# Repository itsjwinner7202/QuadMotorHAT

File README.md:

# QuadMotorHAT

A simple Raspberry Pi HAT for controlling four DC motors.

## Why I made it

While making my WRO robot, I ran into a problem: I needed to control multiple motors from a Raspberry Pi without a mess of separate boards and wiring.

There are already plenty of motor HATs available, but I wanted something simple that fit what I needed. So I decided to design my own.

## Features

* **4 motor control** — Control four motors from the Raspberry Pi using the included Python library.
* **Screw terminals** — Secure connections for the motors and power.
* **Compact design** — Keeps a low profile while leaving enough room for a cooling fan on the Raspberry Pi.
* **Simple Python control** — Control the motors directly from your Python project.

## Python Library

The repository includes `quadmotorhat.py`, which provides a simple interface for controlling the four motors.

First, install `gpiozero`:

```bash
pip install gpiozero
```

Then place `quadmotorhat.py` in the same directory as your Python program:

```text
your_project/
├── quadmotorhat.py
└── main.py
```

Import the motor controls:

```python
from quadmotorhat import M1, M2, M3, M4
```

You can then use `M1`, `M2`, `M3`, and `M4` to control the four motor outputs.

## PCB Files

The full board design is included in the repository.

* `QuadMotorHAT.kicad_sch` — Schematic
* `QuadMotorHAT.kicad_pcb` — PCB layout
* `QuadMotorHAT.kicad_pro` — KiCad project

You can open these files in KiCad to inspect or modify the design.

## License

This project is licensed under the terms of the license included in this repository.

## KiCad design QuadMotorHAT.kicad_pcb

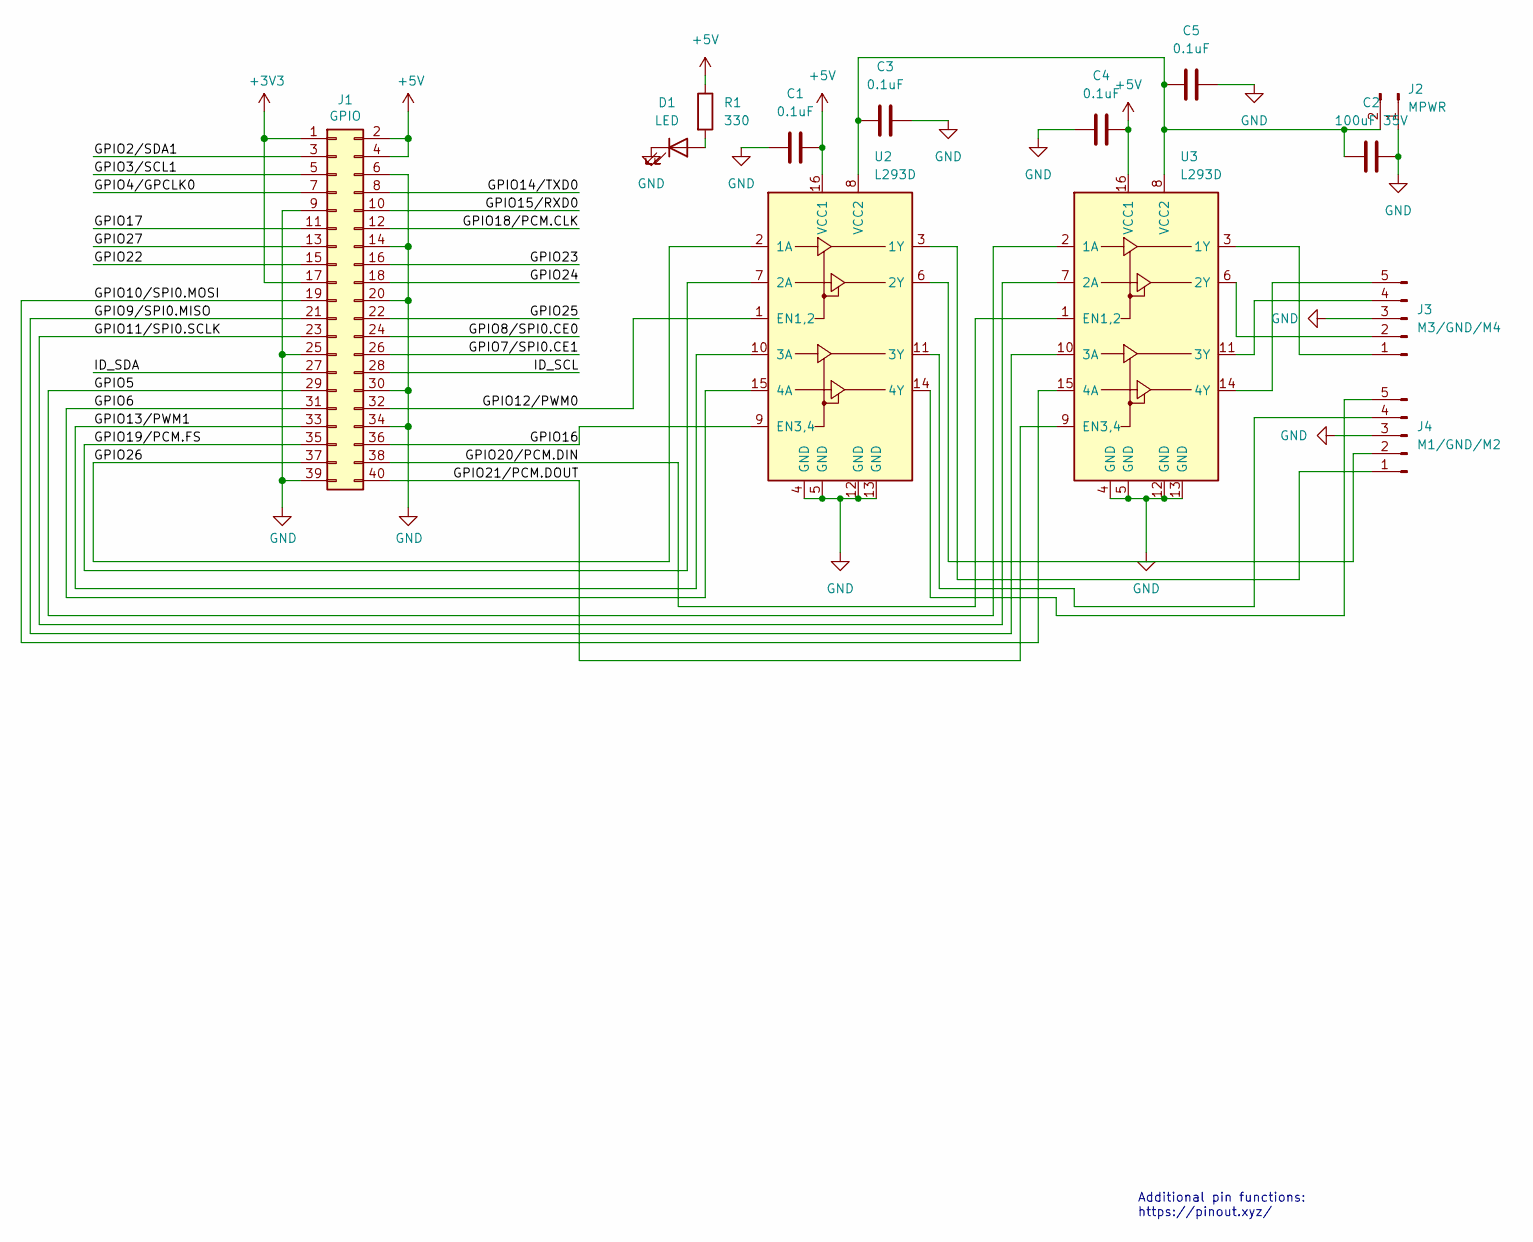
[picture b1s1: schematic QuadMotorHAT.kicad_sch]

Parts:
C1, C3, C4, C5: 0.1uF; C_0805_2012Metric
C2: 100uF 35V; CP_Radial_D6.3mm_P2.50mm
D1: LED; LED_0805_2012Metric
J1: GPIO; PinSocket_2x20_P2.54mm_Vertical
J2: MPWR; TerminalBlock_Phoenix_MKDS-1,5-2_1x02_P5.00mm_Horizontal
J3: M3/GND/M4; TerminalBlock_Phoenix_MKDS-1,5-5_1x05_P5.00mm_Horizontal
J4: M1/GND/M2; TerminalBlock_Phoenix_MKDS-1,5-5_1x05_P5.00mm_Horizontal
R1: 330; R_0805_2012Metric
U2, U3: L293D; DIP-16_W7.62mm

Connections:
+3V3: J1.1, J1.17
+5V: C1.2, C4.2, J1.2, J1.4, R1.1, U2.16 (VCC1), U3.16 (VCC1)
/GPIO2/SDA1: J1.3
/GPIO3/SCL1: J1.5
/GPIO4/GPCLK0: J1.7
/GPIO5: J1.29, U3.2 (1A)
/GPIO6: J1.31, U2.15 (4A)
/GPIO7/SPI0.CE1: J1.26
/GPIO8/SPI0.CE0: J1.24
/GPIO9/SPI0.MISO: J1.21, U3.10 (3A)
/GPIO10/SPI0.MOSI: J1.19, U3.15 (4A)
/GPIO11/SPI0.SCLK: J1.23, U3.7 (2A)
/GPIO12/PWM0: J1.32, U2.1 (EN1,2)
/GPIO13/PWM1: J1.33, U2.10 (3A)
/GPIO14/TXD0: J1.8
/GPIO15/RXD0: J1.10
/GPIO16: J1.36, U2.9 (EN3,4)
/GPIO17: J1.11
/GPIO18/PCM.CLK: J1.12
/GPIO19/PCM.FS: J1.35, U2.7 (2A)
/GPIO20/PCM.DIN: J1.38, U3.1 (EN1,2)
/GPIO21/PCM.DOUT: J1.40, U3.9 (EN3,4)
/GPIO22: J1.15
/GPIO23: J1.16
/GPIO24: J1.18
/GPIO25: J1.22
/GPIO26: J1.37, U2.2 (1A)
/GPIO27: J1.13
/ID_SCL: J1.28
/ID_SDA: J1.27
GND: C1.1, C2.2, C3.2, C4.1, C5.2, D1.1 (K), J1.6, J1.9, J1.14, J1.20, J1.25, J1.30, J1.34, J1.39, J2.1, J3.3, J4.3, U2.4 (GND), U2.5 (GND), U2.12 (GND), U2.13 (GND), U3.4 (GND), U3.5 (GND), U3.12 (GND), U3.13 (GND)
unnamed: D1.2 (A), R1.2
unnamed: C2.1, C3.1, C5.1, J2.2, U2.8 (VCC2), U3.8 (VCC2)
unnamed: J3.1, U3.3 (1Y)
unnamed: J3.2, U3.6 (2Y)
unnamed: J3.4, U3.11 (3Y)
unnamed: J3.5, U3.14 (4Y)
unnamed: J4.1, U2.3 (1Y)
unnamed: J4.2, U2.6 (2Y)
unnamed: J4.4, U2.11 (3Y)
unnamed: J4.5, U2.14 (4Y)

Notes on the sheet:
Additional pin functions: https://pinout.xyz/

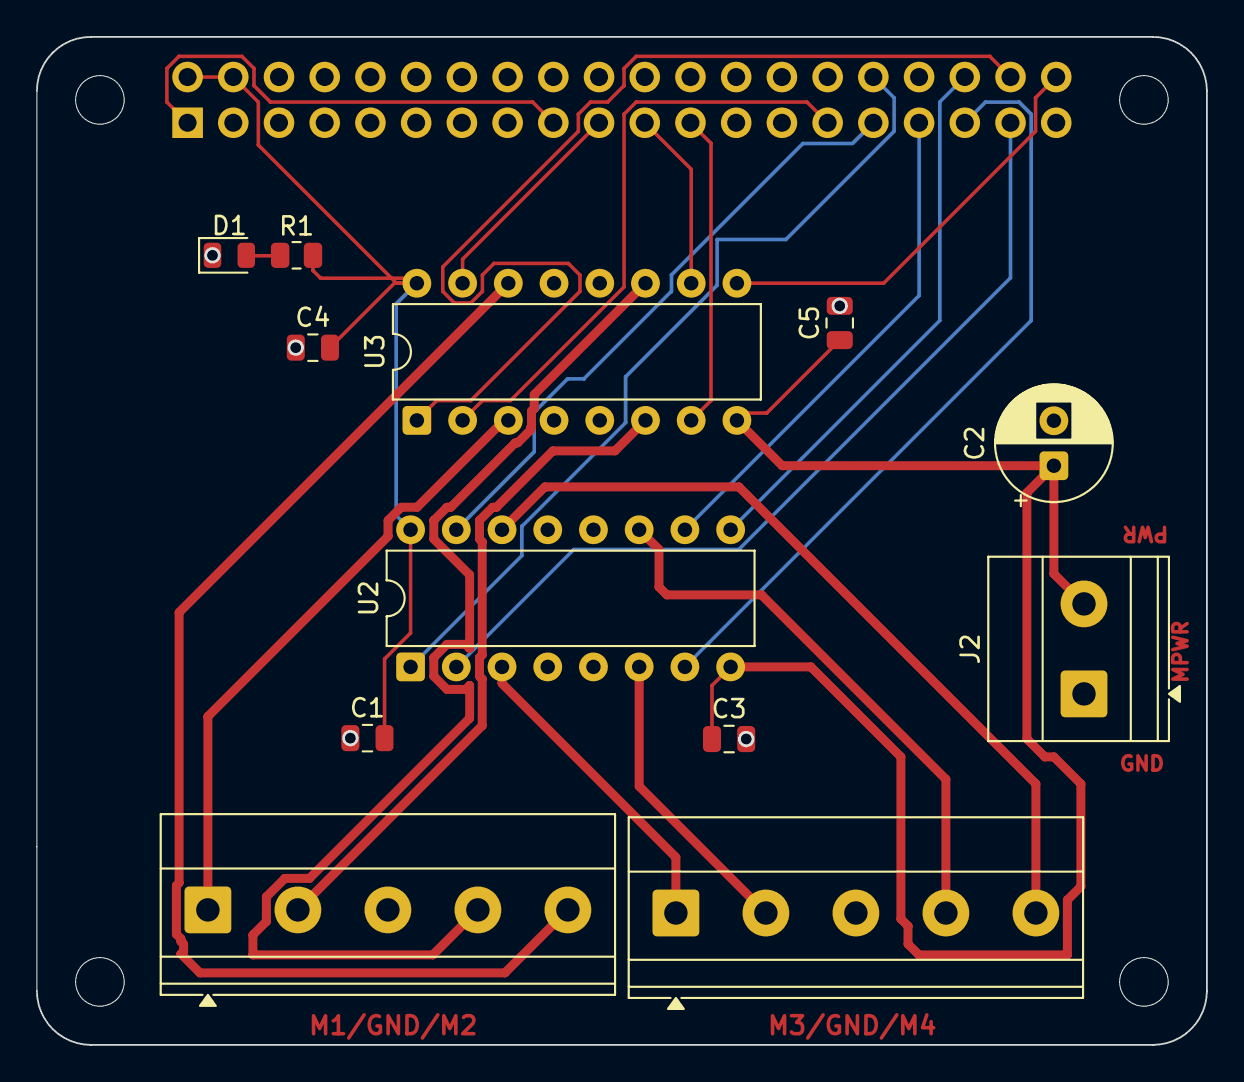
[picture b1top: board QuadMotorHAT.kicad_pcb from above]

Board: 2 copper layers, 65.0 x 56.0 mm, 17 parts (1 on the bottom side), 25 nets.

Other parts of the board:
MH1, MH2, MH3, MH4: MountingHole_2.7mm_M2.5

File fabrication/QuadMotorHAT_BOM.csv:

"Id";"Designator";"Footprint";"Quantity";"Designation";"Supplier and ref";
1;"C1, C3, C4, C5";"C_0805_2012Metric";4;"0.1uF";;;
2;"C2";"CP_Radial_D6.3mm_P2.50mm";1;"100uF 35V";;;
3;"D1";"LED_0805_2012Metric";1;"LED";;;
4;"J1";"PinSocket_2x20_P2.54mm_Vertical";1;"GPIO";;;
5;"J2";"TerminalBlock_Phoenix_MKDS-1,5-2_1x02_P5.00mm_Horizontal";1;"MPWR";;;
6;"J3";"TerminalBlock_Phoenix_MKDS-1,5-5_1x05_P5.00mm_Horizontal";1;"M3/GND/M4";;;
7;"J4";"TerminalBlock_Phoenix_MKDS-1,5-5_1x05_P5.00mm_Horizontal";1;"M1/GND/M2";;;
8;"R1";"R_0805_2012Metric";1;"330";;;
9;"U2, U3";"DIP-16_W7.62mm";2;"L293D";;;
